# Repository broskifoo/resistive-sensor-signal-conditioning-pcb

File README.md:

# Resistive Sensor Signal-Conditioning PCB

A small 2-layer KiCad PCB that reads a 1 kΩ to 10 kΩ resistive sensor and outputs a voltage for a 3.3 V microcontroller ADC. It runs from an external 5 to 12 V DC supply and makes its own 3.3 V rail.

> **Status:** schematic and layout finished, ERC and DRC clean (0 violations, 0 unconnected items, schematic parity OK). **Not yet fabricated or tested on hardware.**

## What it does

1. **Power:** a TI LMR36510ADDA buck regulator turns the 5 to 12 V input into 3.3 V. The feedback divider is 100 kΩ / 43.2 kΩ with the 1 V feedback reference from the datasheet, which gives about 3.315 V.
2. **Sensor divider:** 3.3 V → R1 (10 kΩ) → sense node → sensor → GND. The sense voltage is about 0.30 V at 1 kΩ and 1.65 V at 10 kΩ.
3. **Scaling:** half of a TI TLV9002 dual op-amp (U1A) is a non-inverting amplifier with gain 2.3 and an offset. The other half (U1B) buffers a reference voltage of about 0.458 V made by a 62 kΩ / 10 kΩ divider from 3.3 V.
4. **Filter:** a 1 kΩ + 1 µF low-pass filter (about 159 Hz cutoff) sits at the output.

Ideal output: `Vout = 2.3 × Vsense − 1.3 × Vref`

| Sensor resistance | Sense voltage | Output voltage |
|---|---|---|
| 1 kΩ | 0.30 V | about 0.09 V |
| 10 kΩ | 1.65 V | about 3.20 V |

The output range is kept slightly inside 0 to 3.3 V because the TLV9002 output cannot swing all the way to the rails. Use 1% resistors. Real values will shift a little with tolerance.

## Connectors

| Connector | Pin 1 | Pin 2 | Pin 3 |
|---|---|---|---|
| J1 (sensor) | Sense node | GND | - |
| J2 (output) | Signal out (to ADC) | 3.3 V | GND |
| J3 (power in) | +5 to 12 V | GND | - |

## Main parts

| Ref | Part |
|---|---|
| U1 | TLV9002IDR dual op-amp, SOIC-8 |
| U2 | LMR36510ADDA buck regulator |
| L1 | 22 µH inductor (footprint: Bourns SRN6045TA, see to-do list) |
| C3, C4 | Input capacitors, 2.2 µF and 220 nF |
| C7, C8, C9 | 22 µF output capacitors |
| R, C (others) | 0805 SMD |

## Board notes

- 2 layers: signals and power on top, a continuous GND plane on the bottom.
- GND pads connect to the plane through vias. U2's exposed pad has thermal vias.
- The 3.3 V trace to the sensor side hops under another trace on the bottom layer.
- Trace widths: 0.5 mm for power, 0.25 mm for small signals.

## Files

| File | What it is |
|---|---|
| `Resistive_Sensor_PCB.kicad_sch` | Schematic |
| `Resistive_Sensor_PCB.kicad_pcb` | PCB layout |
| `Resistive_Sensor_PCB.kicad_pro` | KiCad project file |
| `gerbers/` | Gerber and drill files for manufacturing |

Made with KiCad 10.0.7.

## To do before ordering

- [ ] Confirm the L1 footprint matches the exact inductor that will be bought (size and current rating).
- [ ] Use capacitors rated at least 25 V for C3 and C4 (they sit on the 12 V input).
- [ ] Remove the leftover `TLV9002` project footprint library entry (it points to a file on the author's computer and is not used).
- [ ] Build one board and measure the output at 1 kΩ and 10 kΩ.

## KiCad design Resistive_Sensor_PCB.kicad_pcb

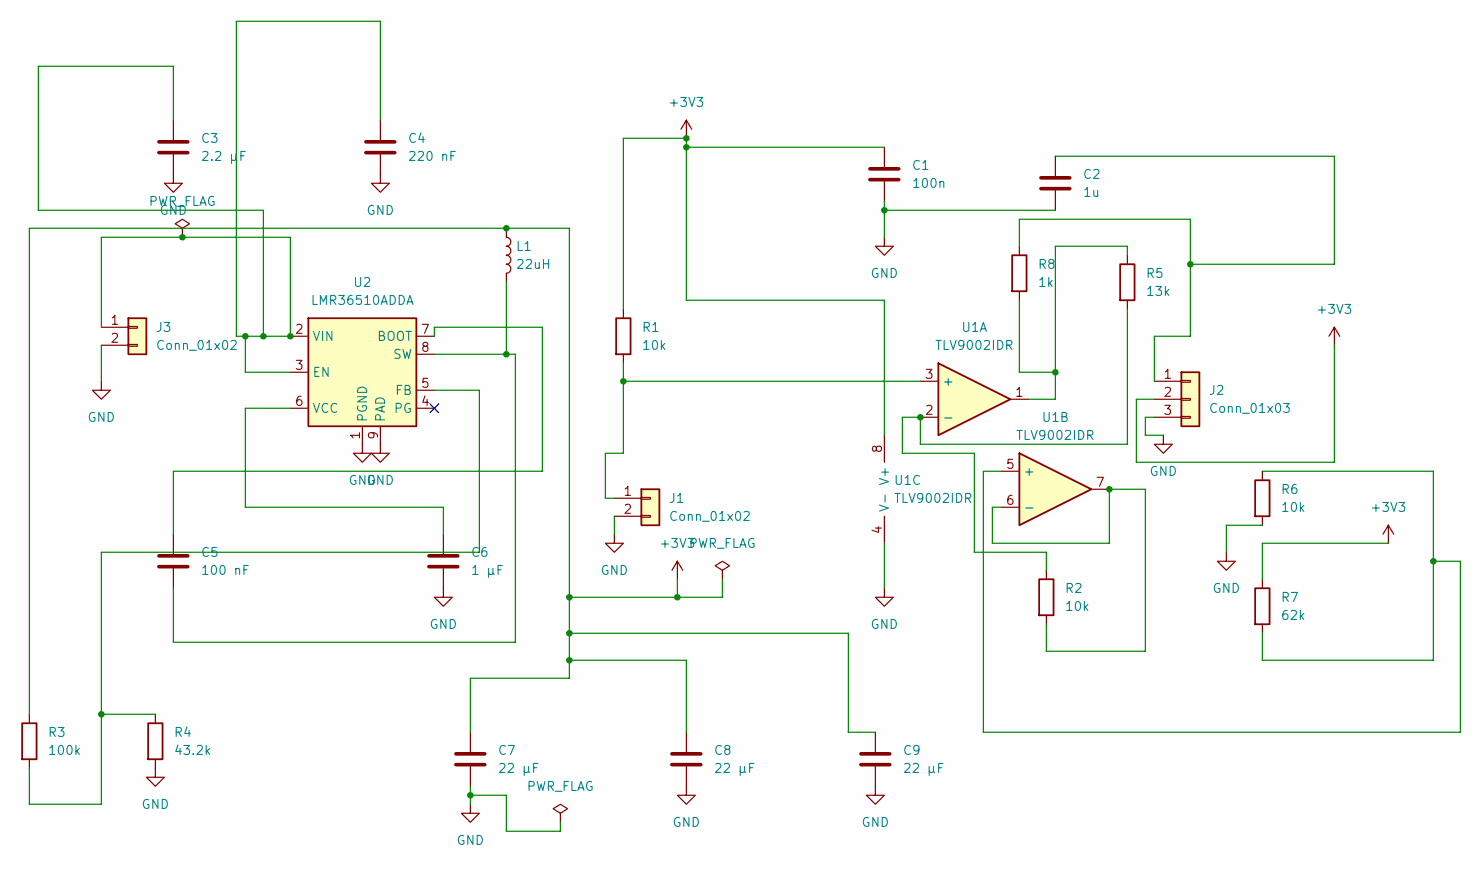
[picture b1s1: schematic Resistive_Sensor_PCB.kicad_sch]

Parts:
C1: 100n; C_0805_2012Metric
C2: 1u; C_0805_2012Metric
C3: 2.2 µF; C_0805_2012Metric
C4: 220 nF; C_0805_2012Metric
C5: 100 nF; C_0805_2012Metric
C6: 1 µF; C_0805_2012Metric
C7, C8, C9: 22 µF; C_0805_2012Metric
J1, J3: Conn_01x02; PinHeader_1x02_P2.54mm_Vertical
J2: Conn_01x03; PinHeader_1x03_P2.54mm_Vertical
L1: 22uH; L_Bourns_SRN6045TA
R1, R2, R6: 10k; R_0805_2012Metric
R3: 100k; R_0805_2012Metric
R4: 43.2k; R_0805_2012Metric
R5: 13k; R_0805_2012Metric
R7: 62k; R_0805_2012Metric
R8: 1k; R_0805_2012Metric
U1: TLV9002IDR; SOIC-8_3.9x4.9mm_P1.27mm
U2: LMR36510ADDA; Texas_HTSOP-8-1EP_3.9x4.9mm_P1.27mm_EP2.95x4.9mm_Mask2.4x3.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

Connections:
+3V3: C1.1, C7.1, C8.1, C9.1, J2.2, L1.1, R1.1, R3.1, R7.1, U1.8 (V+)
GND: C1.2, C2.2, C3.2, C4.2, C6.2, C7.2, C8.2, C9.2, J1.2, J2.3, J3.2, R4.2, R6.2, U1.4 (V-), U2.1 (PGND), U2.9 (PAD)
unnamed: J1.1, R1.2, U1.3 (+)
unnamed: C2.1, J2.1, R8.1
unnamed: C3.1, C4.1, J3.1, U2.2 (VIN), U2.3 (EN)
unnamed: R5.1, R8.2, U1.1
unnamed: R2.1, R5.2, U1.2 (-)
unnamed: R6.1, R7.2, U1.5 (+)
unnamed: R2.2, U1.6 (-), U1.7
unnamed: C5.1, U2.7 (BOOT)
unnamed: R3.2, R4.1, U2.5 (FB)
unnamed: C5.2, L1.2, U2.8 (SW)
unnamed: C6.1, U2.6 (VCC)

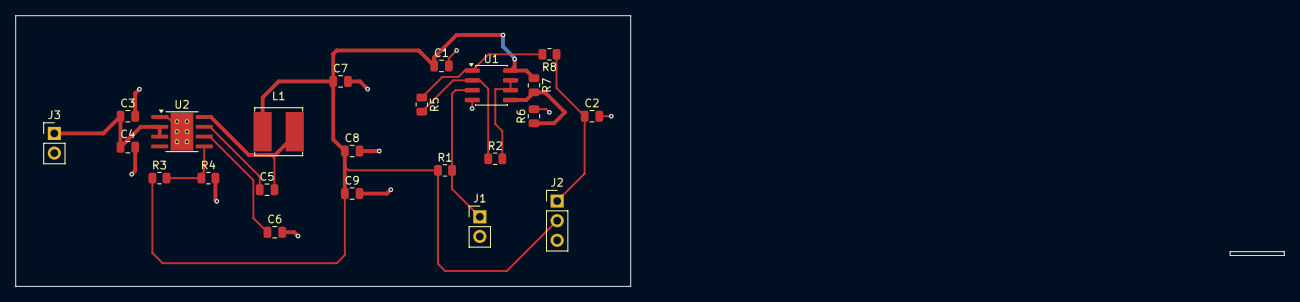
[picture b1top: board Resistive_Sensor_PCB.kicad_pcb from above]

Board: 2 copper layers, 79.5 x 35.0 mm, 23 parts (0 on the bottom side), 13 nets.
